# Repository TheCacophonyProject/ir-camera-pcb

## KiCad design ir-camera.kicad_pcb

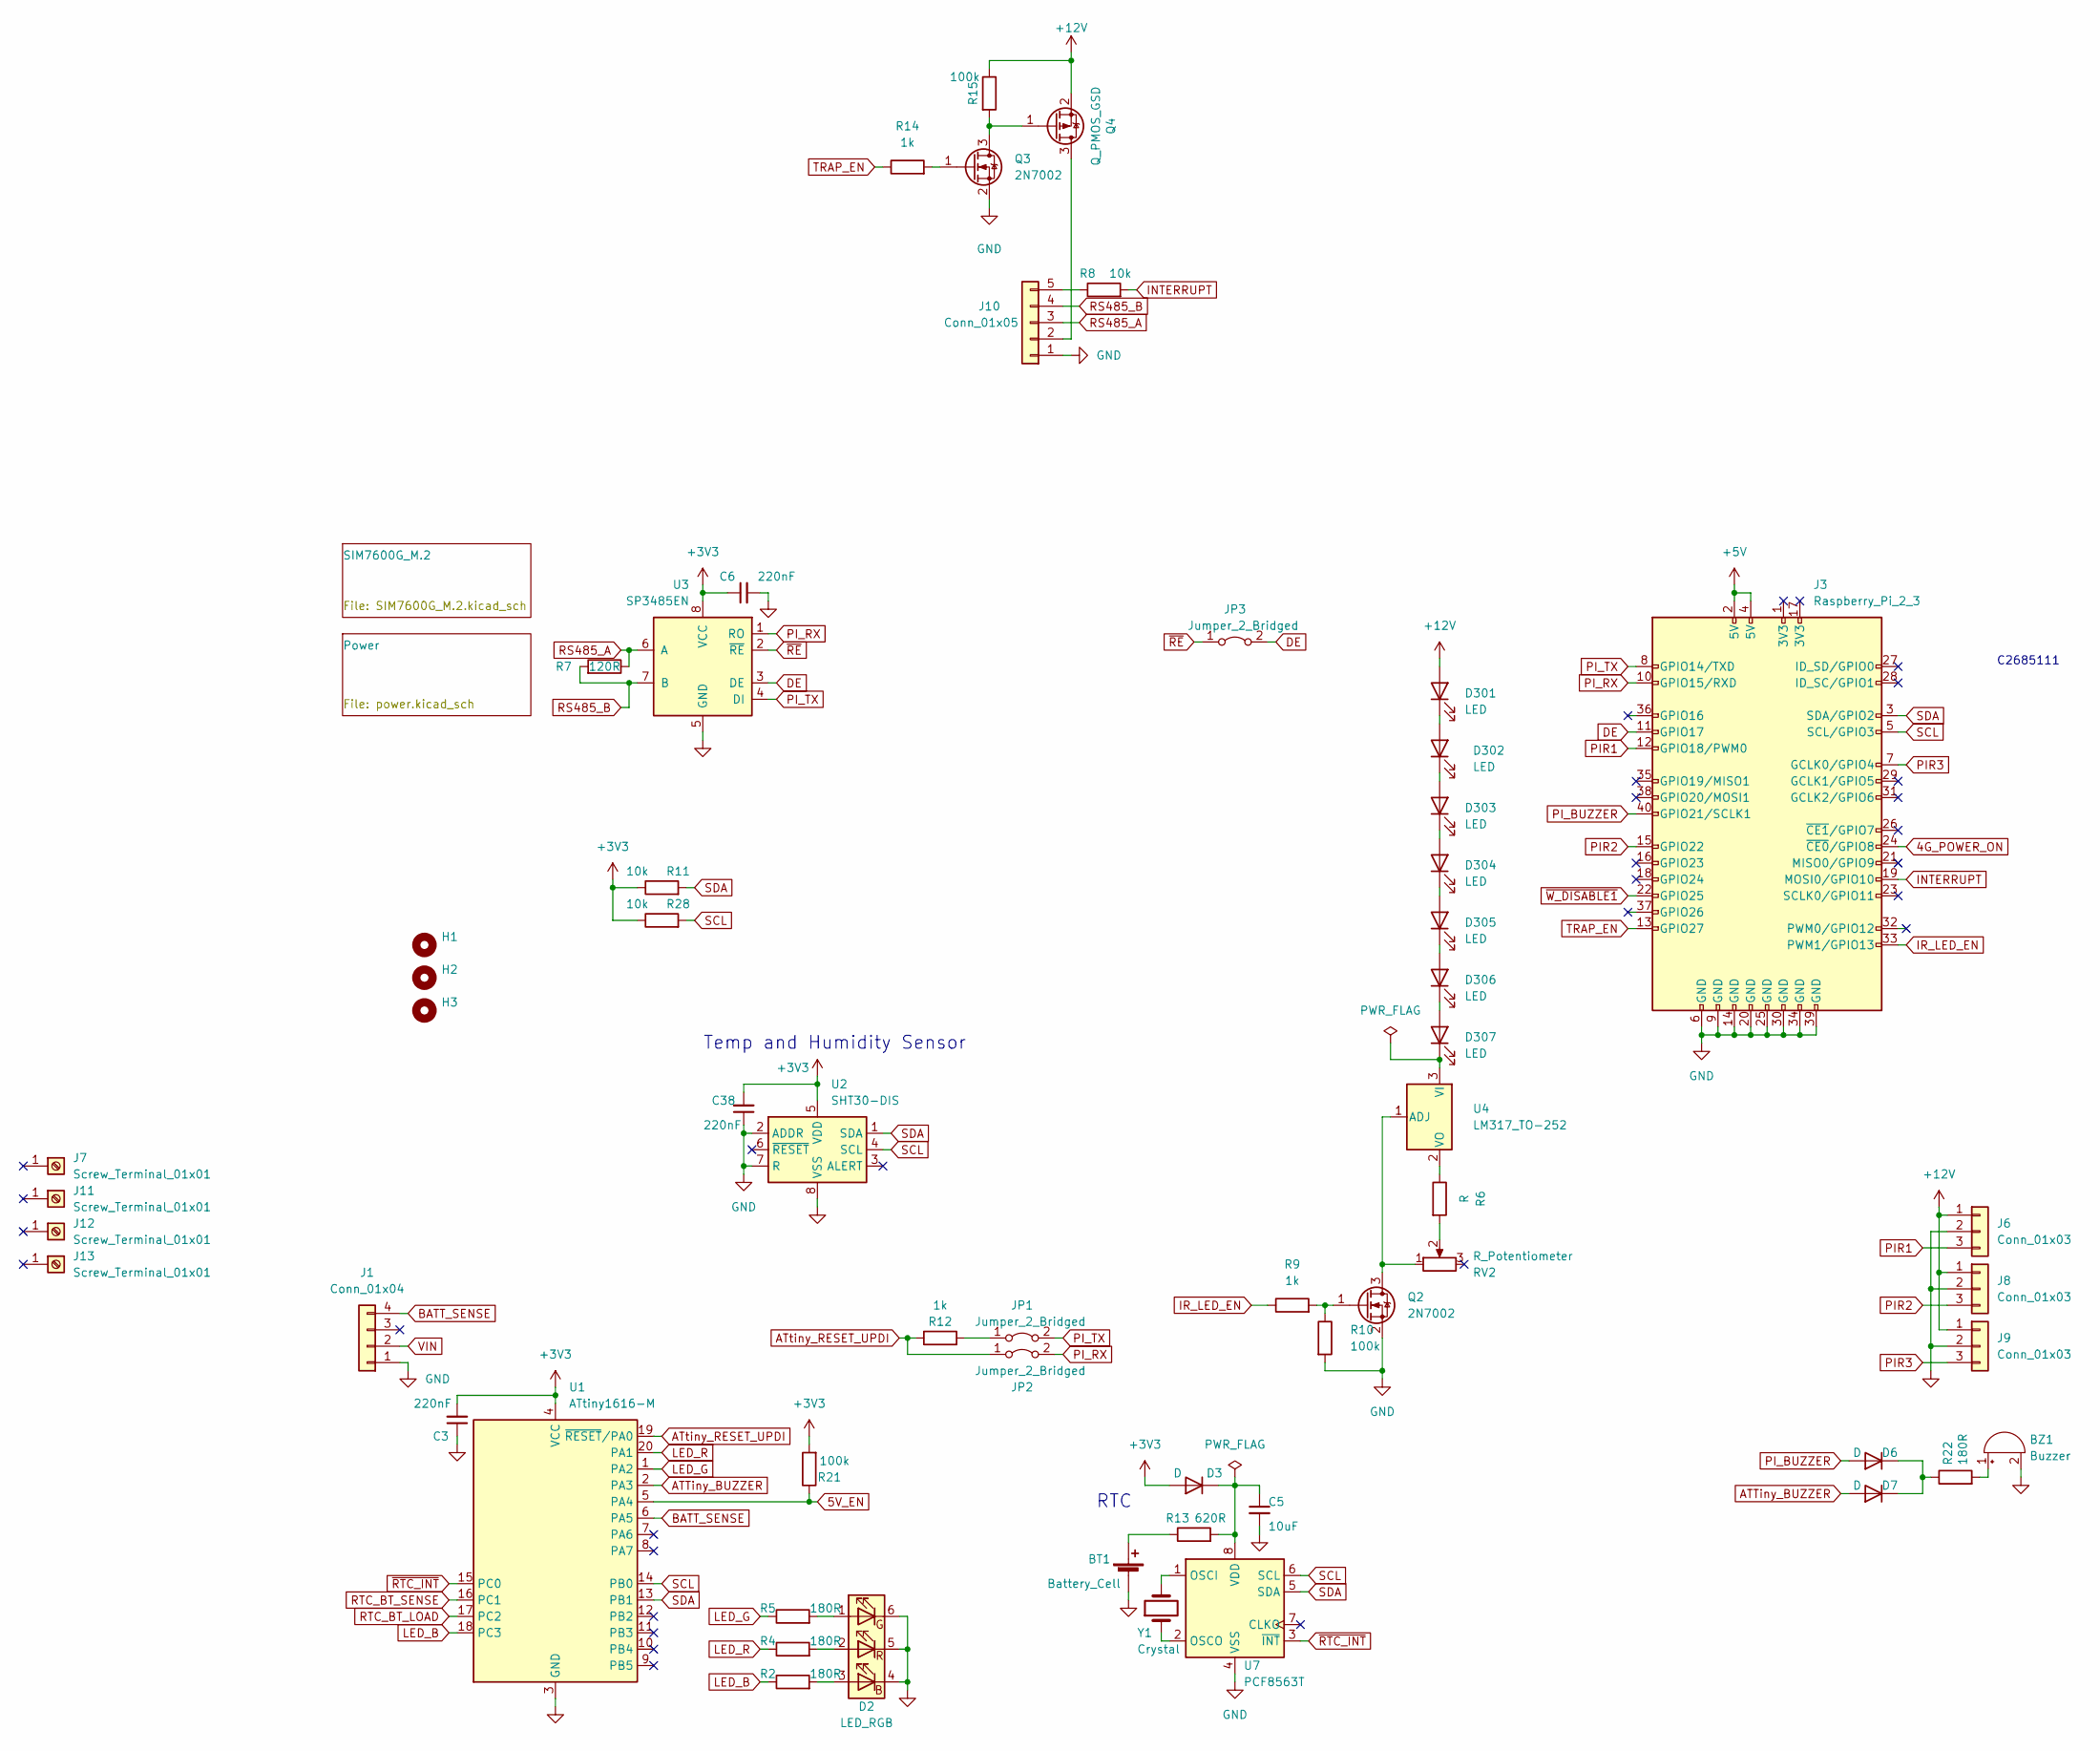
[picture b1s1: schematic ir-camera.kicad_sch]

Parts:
BT1: Battery_Cell; CAP-SMD_FL11E
BZ1: Buzzer; BUZ-TH_BD9.0-P5.00-D0.6-FD; LCSC C96102
C3, C6, C38: 220nF; C_0402_1005Metric; LCSC C16772
C5: 10uF; C_0603_1608Metric; LCSC C19702
D2: LED_RGB; LED-SMD_6PIN-L1.60-W1.50-BL-RD; LCSC C375568
D3, D6, D7: D; D_SOD-523; LCSC C668989
D301, D302, D303, D304, D305, D306, D307: LED; OPTO-SMD_L2.0-W1.4-R-RD; LCSC C282225
H1, H2, H3: MountingHole; Mouning_Hole_M3
J1: Conn_01x04; JST_XA_B04B-XASK-1_1x04_P2.50mm_Vertical
J3: Raspberry_Pi_2_3; HDR-SMD_40P-P2.54-V-F-R2-C20-S8.7-EH; LCSC C2685111
J6, J8, J9: Conn_01x03; CONN-TH_B03B-XASK-1-A-LF-SN
J7, J11, J12, J13: Screw_Terminal_01x01; SMD_BD4.4-L4.4-D2.8; LCSC C2928176
J10: Conn_01x05; JST_XA_B05B-XASK-1-A_1x05_P2.50mm_Vertical; LCSC C493429
JP1, JP2, JP3: Jumper_2_Bridged; PinHeader_1x02_P2.54mm_Vertical
Q2, Q3: 2N7002; SOT-23; LCSC C8545
Q4: Q_PMOS_GSD; SOT-23; LCSC C15127
R2, R4, R5, R22: 180R; R_0402_1005Metric; LCSC C38941
R6: R; R_0603_1608Metric; LCSC C25190
R7: 120R; R_0402_1005Metric; LCSC C25079
R8, R11, R28: 10k; R_0402_1005Metric; LCSC C25744
R9, R12, R14: 1k; R_0402_1005Metric; LCSC C11702
R10, R15, R21: 100k; R_0402_1005Metric; LCSC C25741
R13: 620R; R_0603_1608Metric; LCSC C23220
RV2: R_Potentiometer; RES-ADJ-SMD_VG039NCH; LCSC C128542
U1: ATtiny1616-M; VQFN-20-1EP_3x3mm_P0.4mm_EP1.7x1.7mm; LCSC C507118
U2: SHT30-DIS; Sensirion_DFN-8-1EP_2.5x2.5mm_P0.5mm_EP1.1x1.7mm; LCSC C77361
U3: SP3485EN; SOIC-8_3.9x4.9mm_P1.27mm; LCSC C8963
U4: LM317_TO-252; TO-252-2; LCSC C75510
U7: PCF8563T; SOIC-8_3.9x4.9mm_P1.27mm; LCSC C7440
Y1: Crystal; Crystal_SMD_3215-2Pin_3.2x1.5mm; LCSC C32346

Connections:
4G_POWER_ON: J3.24 (~CE0/GPIO8); also elsewhere on the board
5V_EN: R21.1, U1.5 (PA4); also elsewhere on the board
+3V3: C3.2, C6.1, C38.2, D3.2 (A), R11.1, R21.2, R28.1, U1.4 (VCC), U2.5 (VDD), U3.8 (VCC); also elsewhere on the board
+5V: J3.2 (5V), J3.4 (5V); also elsewhere on the board
+12V: D301.2 (A), J6.1, J8.1, J9.1, Q4.2 (S), R15.1; also elsewhere on the board
ATTiny_BUZZER: D7.2 (A), U1.2 (PA3)
ATtiny_RESET_UPDI: JP2.1 (A), R12.1, U1.19 (~RESET/PA0)
BATT_SENSE: J1.4, U1.6 (PA5)
DE: J3.11 (GPIO17), JP3.2 (B), U3.3 (DE)
GND: BT1.2 (-), BZ1.2 (+), C3.1, C5.2, C6.2, C38.1, D2.4 (BK), D2.5 (GK), D2.6 (RK), J1.1, J3.6 (GND), J3.9 (GND), J3.14 (GND), J3.20 (GND), J3.25 (GND), J3.30 (GND), J3.34 (GND), J3.39 (GND), J6.2, J8.2, J9.2, J10.1, Q2.2 (S), Q3.2 (S), R10.2, U1.3 (GND), U1.21 (GND), U2.2 (ADDR), U2.7 (R), U2.8 (VSS), U2.9 (VSS), U3.5 (GND), U7.4 (VSS); also elsewhere on the board
INTERRUPT: J3.19 (MOSI0/GPIO10), R8.2
IR_LED_EN: J3.33 (PWM1/GPIO13), R9.1
LED_B: R2.1, U1.18 (PC3)
LED_G: R5.1, U1.1 (PA2)
LED_R: R4.1, U1.20 (PA1)
unnamed: BZ1.1 (-), R22.2
unnamed: C5.1, D3.1 (K), R13.2, U7.8 (VDD)
unnamed: D2.1 (RA), R5.2
unnamed: D2.2 (GA), R4.2
unnamed: D2.3 (BA), R2.2
unnamed: D6.1 (K), D7.1 (K), R22.1
unnamed: D301.1 (K), D302.2 (A)
unnamed: D302.1 (K), D303.2 (A)
unnamed: D303.1 (K), D304.2 (A)
unnamed: D304.1 (K), D305.2 (A)
unnamed: D305.1 (K), D306.2 (A)
unnamed: D306.1 (K), D307.2 (A)
unnamed: D307.1 (K), U4.3 (VI)
unnamed: J10.2, Q4.3 (D)
unnamed: J10.5, R8.1
unnamed: JP1.1 (A), R12.2
unnamed: Q2.1 (G), R9.2, R10.1
unnamed: Q2.3 (D), RV2.1, U4.1 (ADJ)
unnamed: Q3.1 (G), R14.2
unnamed: Q3.3 (D), Q4.1 (G), R15.2
unnamed: R6.1, U4.2 (VO)
unnamed: R6.2, RV2.2
unnamed: U7.1 (OSCI), Y1.2
unnamed: U7.2 (OSCO), Y1.1
PIR1: J3.12 (GPIO18/PWM0), J6.3
PIR2: J3.15 (GPIO22), J8.3
PIR3: J3.7 (GCLK0/GPIO4), J9.3
PI_BUZZER: D6.2 (A), J3.40 (GPIO21/SCLK1)
PI_RX: J3.10 (GPIO15/RXD), JP2.2 (B), U3.1 (RO)
PI_TX: J3.8 (GPIO14/TXD), JP1.2 (B), U3.4 (DI)
RS485_A: J10.3, R7.1, U3.6 (A)
RS485_B: J10.4, R7.2, U3.7 (B)
RTC_BT_LOAD: U1.17 (PC2); also elsewhere on the board
SCL: J3.5 (SCL/GPIO3), R28.2, U1.14 (PB0), U2.4 (SCL), U7.6 (SCL)
SDA: J3.3 (SDA/GPIO2), R11.2, U1.13 (PB1), U2.1 (SDA), U7.5 (SDA)
TRAP_EN: J3.13 (GPIO27), R14.1
VIN: J1.2; also elsewhere on the board
~RE: JP3.1 (A), U3.2 (~RE)
~RTC_INT: U1.15 (PC0), U7.3 (~INT)
~W_DISABLE1: J3.22 (GPIO25); also elsewhere on the board

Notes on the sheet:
C2685111
RTC
Temp and Humidity Sensor

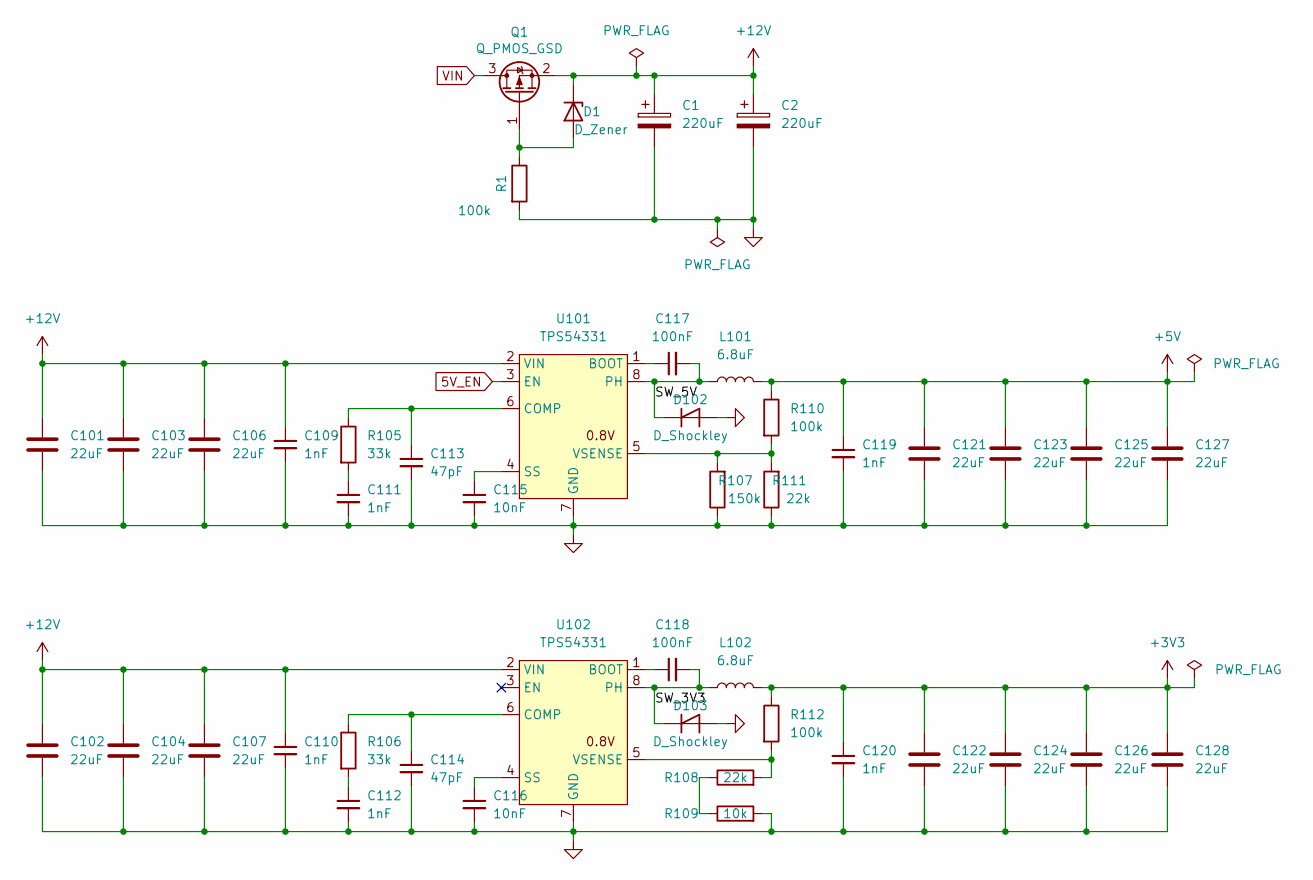
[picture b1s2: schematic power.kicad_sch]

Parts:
C1, C2: 220uF; CP_Elec_8x10; LCSC C2895286
C101, C102, C103, C104, C106, C107: 22uF; C_0805_2012Metric; LCSC C602037
C109, C110, C111, C112, C119, C120: 1nF; C_0402_1005Metric; LCSC C1523
C113, C114: 47pF; C_0402_1005Metric; LCSC C1567
C115, C116: 10nF; C_0402_1005Metric; LCSC C15195
C117, C118: 100nF; C_0402_1005Metric; LCSC C307331
C121, C122, C123, C124, C125, C126, C127, C128: 22uF; C_0603_1608Metric; LCSC C86295
D1: D_Zener; LL-34_L3.5-W1.5-RD; LCSC C8062
D102, D103: D_Shockley; D_SMA; LCSC C22452
L101, L102: 6.8uF; IND-SMD_L8.0-W8.0_1217AS; LCSC C83465
Q1: Q_PMOS_GSD; SOT-23; LCSC C15127
R1, R110, R112: 100k; R_0402_1005Metric; LCSC C25741
R105, R106: 33k; R_0402_1005Metric; LCSC C25779
R107: 150k; R_0402_1005Metric; LCSC C25755
R108, R111: 22k; R_0402_1005Metric; LCSC C25768
R109: 10k; R_0402_1005Metric; LCSC C25744
U101, U102: TPS54331; SO-8_3.9x4.9mm_P1.27mm; LCSC C9865

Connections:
5V_EN: U101.3 (EN); also elsewhere on the board
+3V3: C120.1, C122.1, C124.1, C126.1, C128.1, L102.2, R112.1; also elsewhere on the board
+5V: C119.1, C121.1, C123.1, C125.1, C127.1, L101.2, R110.1; also elsewhere on the board
+12V: C1.1, C2.1, C101.1, C102.1, C103.1, C104.1, C106.1, C107.1, C109.1, C110.1, D1.1 (K), Q1.2 (S), U101.2 (VIN), U102.2 (VIN); also elsewhere on the board
/Power/SW_3V3: C118.2, D103.1 (K), L102.1, U102.8 (PH)
/Power/SW_5V: C117.2, D102.1 (K), L101.1, U101.8 (PH)
GND: C1.2, C2.2, C101.2, C102.2, C103.2, C104.2, C106.2, C107.2, C109.2, C110.2, C111.2, C112.2, C113.2, C114.2, C115.2, C116.2, C119.2, C120.2, C121.2, C122.2, C123.2, C124.2, C125.2, C126.2, C127.2, C128.2, D102.2 (A), D103.2 (A), R1.2, R107.1, R109.2, R111.1, U101.7 (GND), U102.7 (GND); also elsewhere on the board
unnamed: C111.1, R105.2
unnamed: C112.1, R106.2
unnamed: C113.1, R105.1, U101.6 (COMP)
unnamed: C114.1, R106.1, U102.6 (COMP)
unnamed: C115.1, U101.4 (SS)
unnamed: C116.1, U102.4 (SS)
unnamed: C117.1, U101.1 (BOOT)
unnamed: C118.1, U102.1 (BOOT)
unnamed: D1.2 (A), Q1.1 (G), R1.1
unnamed: R107.2, R110.2, R111.2, U101.5 (VSENSE)
unnamed: R108.1, R109.1
unnamed: R108.2, R112.2, U102.5 (VSENSE)
VIN: Q1.3 (D); also elsewhere on the board

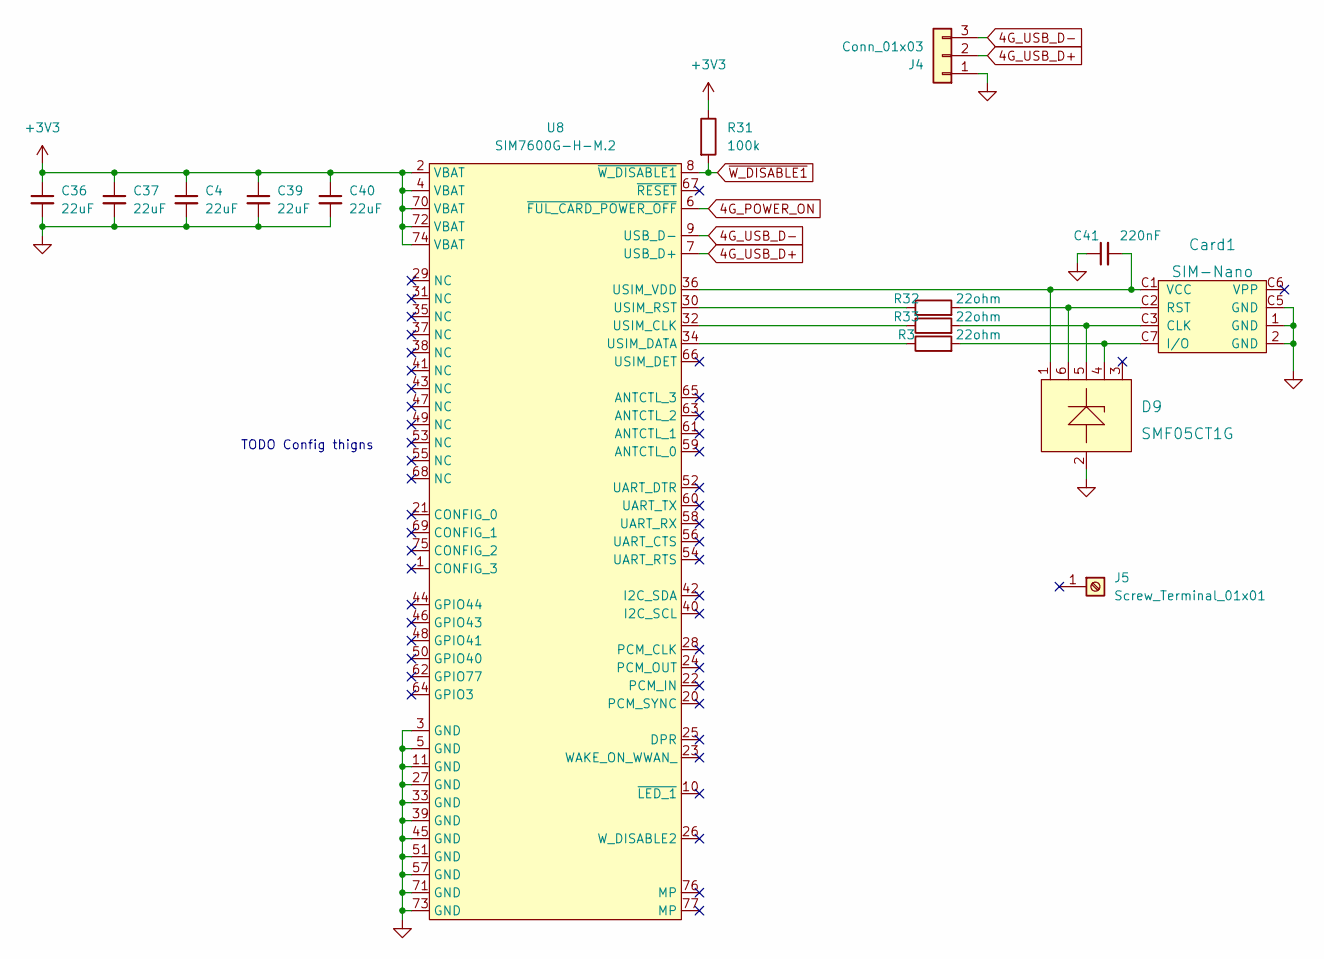
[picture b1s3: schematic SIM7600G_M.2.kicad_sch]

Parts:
C4, C36, C37, C39, C40: 22uF; C_0603_1608Metric; LCSC C86295
C41: 220nF; C_0402_1005Metric; LCSC C16772
Card1: SIM-Nano; LCSC C266889
D9: SMF05CT1G; SOT-363_L2.0-W1.3-P0.65-LS2.1-TL; LCSC C15879
J4: Conn_01x03; PinHeader_1x03_P2.54mm_Vertical
J5: Screw_Terminal_01x01; SMD_BD4.4-L4.4-D2.8; LCSC C2928178
R3, R32, R33: 22ohm; R_0402_1005Metric; LCSC C25092
R31: 100k; R_0402_1005Metric; LCSC C25741
U8: SIM7600G-H-M.2; M.2; LCSC C2761526

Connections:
4G_POWER_ON: U8.6 (~FUL_CARD_POWER_OFF); also elsewhere on the board
4G_USB_D+: J4.2, U8.7 (USB_D+)
4G_USB_D-: J4.3, U8.9 (USB_D-)
+3V3: C4.1, C36.1, C37.1, C39.1, C40.1, R31.1, U8.2 (VBAT), U8.4 (VBAT), U8.70 (VBAT), U8.72 (VBAT), U8.74 (VBAT); also elsewhere on the board
GND: C4.2, C36.2, C37.2, C39.2, C40.2, C41.1, Card1.1 (GND), Card1.2 (GND), Card1.C5 (GND), D9.2, J4.1, U8.3 (GND), U8.5 (GND), U8.11 (GND), U8.27 (GND), U8.33 (GND), U8.39 (GND), U8.45 (GND), U8.51 (GND), U8.57 (GND), U8.71 (GND), U8.73 (GND); also elsewhere on the board
unnamed: C41.2, Card1.C1 (VCC), D9.1, U8.36 (USIM_VDD)
unnamed: Card1.C2 (RST), D9.6, R32.2
unnamed: Card1.C3 (CLK), D9.5, R33.2
unnamed: Card1.C7 (I/O), D9.4, R3.2
unnamed: R3.1, U8.34 (USIM_DATA)
unnamed: R32.1, U8.30 (USIM_RST)
unnamed: R33.1, U8.32 (USIM_CLK)
~W_DISABLE1: R31.2, U8.8 (~W_DISABLE1); also elsewhere on the board

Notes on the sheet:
TODO Config thigns

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
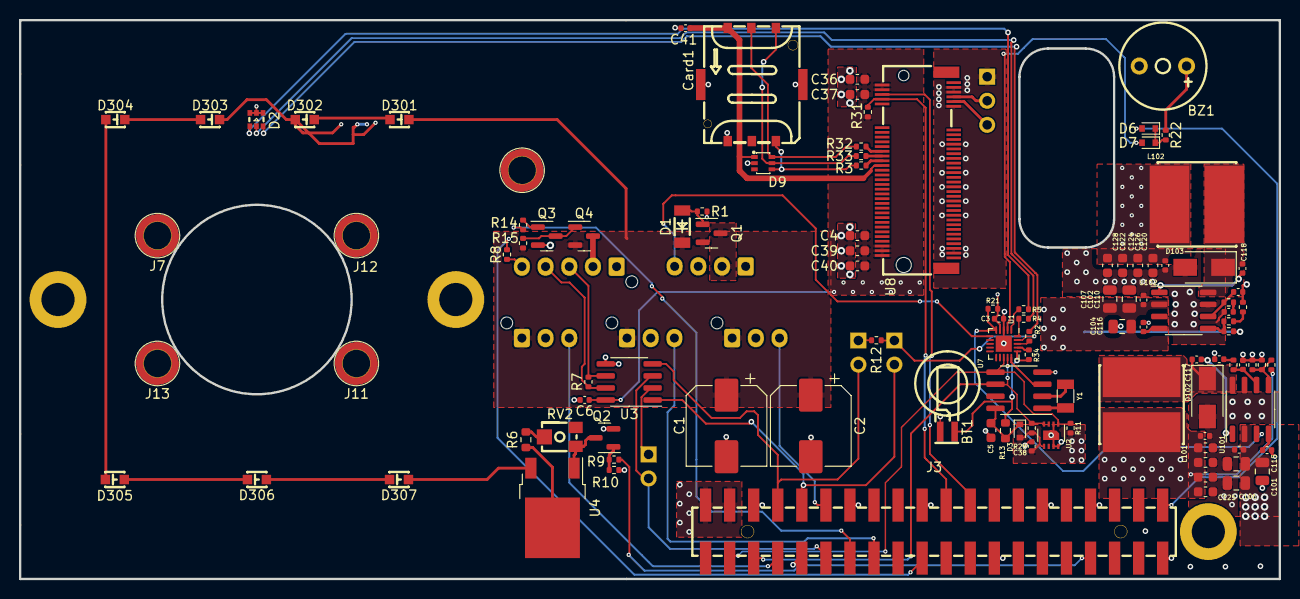
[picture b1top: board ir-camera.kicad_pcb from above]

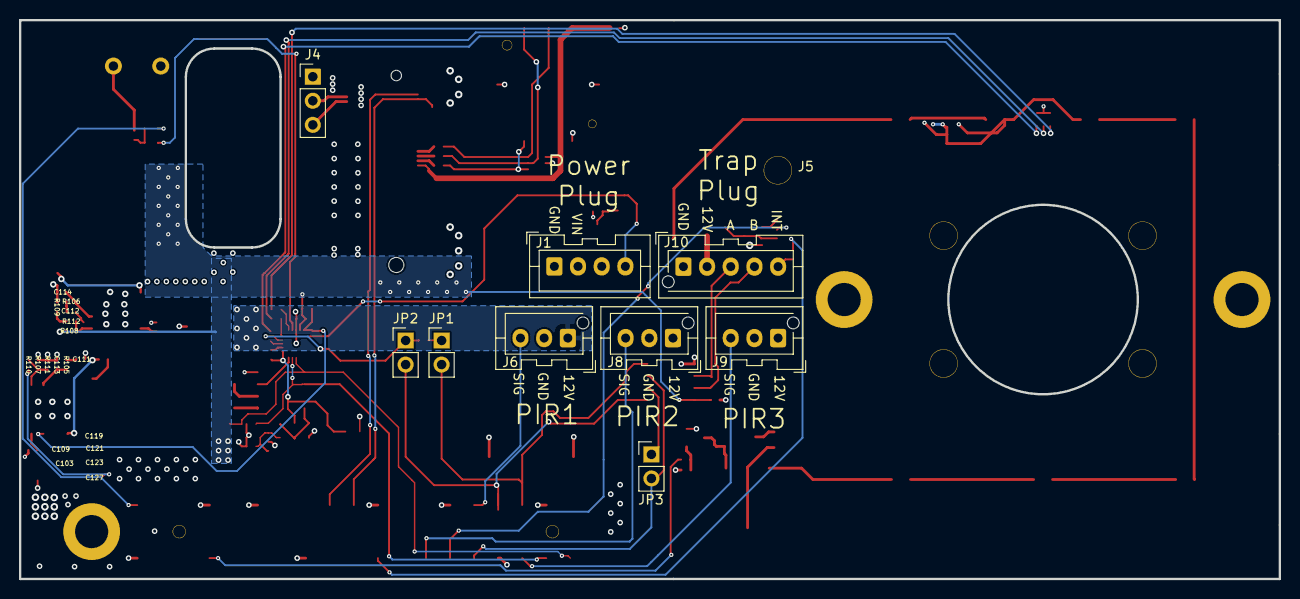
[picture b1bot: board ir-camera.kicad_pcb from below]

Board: 4 copper layers, 133.0 x 59.0 mm, 120 parts (9 on the bottom side), 79 nets.

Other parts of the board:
R34: 10k; R_0402_1005Metric

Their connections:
RTC_BT_LOAD: R34.1; also elsewhere on the board
